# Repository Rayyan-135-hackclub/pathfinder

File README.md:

# pathfinder
Making a PCB for the first time

## Update 1: 6/11/25 Thursday 15 working time

I have started work on the PCB but I have got an error message as I was trying to download the code for the lights. Will try later or in school.
Also hackatime is not recording the time I put into this project and gives error message "Repo url is not clonable." It needs to be sorted out next hackclub.

## Update 2: 7/11/25 Friday 30m working time
Error fixed and I added resistors and wires (in the form of buttons) to the components. I think I have completed the PCB. I made a mistake and deleted everything but I restored it. (most of the time im figuring out what went wrong so it may not be recorded)

Finished Schematic:

## Update 3: 17/11/25 Saturday 20m working time

Watching the video: https://www.youtube.com/watch?v=MFTP7uMzt1s and trying to figure out how to arrange the wires on the PCB editor. Will continue next time.

What I have done so far:

## Update 4: 19/11/25 Wednesday 20m working time

I have completed the routing and I am cuurrently starting the 3D stuff.

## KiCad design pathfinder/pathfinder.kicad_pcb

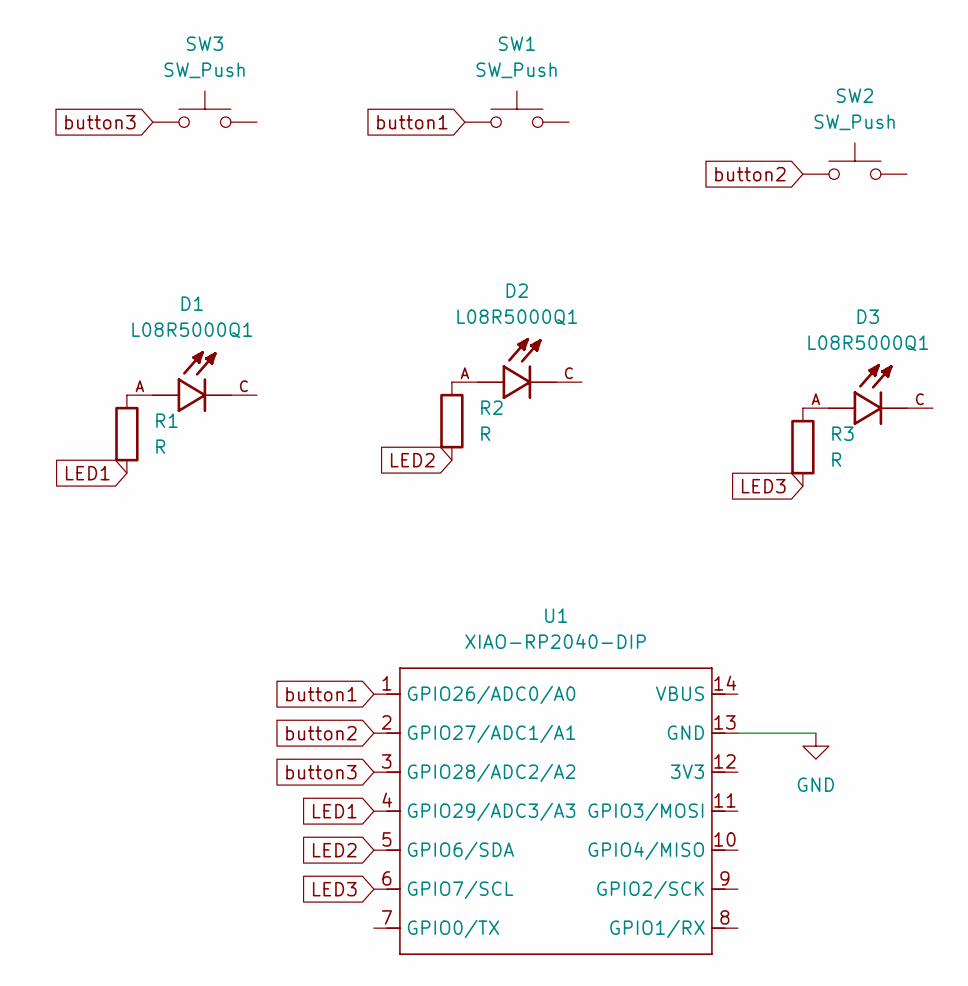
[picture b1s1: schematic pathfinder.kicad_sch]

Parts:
D1, D2, D3: L08R5000Q1; LEDRD254W57D500H1070; PARTREV NA
R1, R2, R3: R; R_Axial_DIN0204_L3.6mm_D1.6mm_P7.62mm_Horizontal
SW1, SW2, SW3: SW_Push; SW_Cherry_MX_1.00u_PCB
U1: XIAO-RP2040-DIP

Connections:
GND: U1.13 (GND)
LED1: R1.2, U1.4 (GPIO29/ADC3/A3)
LED2: R2.2, U1.5 (GPIO6/SDA)
LED3: R3.2, U1.6 (GPIO7/SCL)
unnamed: D1.A, R1.1
unnamed: D2.A, R2.1
unnamed: D3.A, R3.1
button1: SW1.1, U1.1 (GPIO26/ADC0/A0)
button2: SW2.1, U1.2 (GPIO27/ADC1/A1)
button3: SW3.1, U1.3 (GPIO28/ADC2/A2)

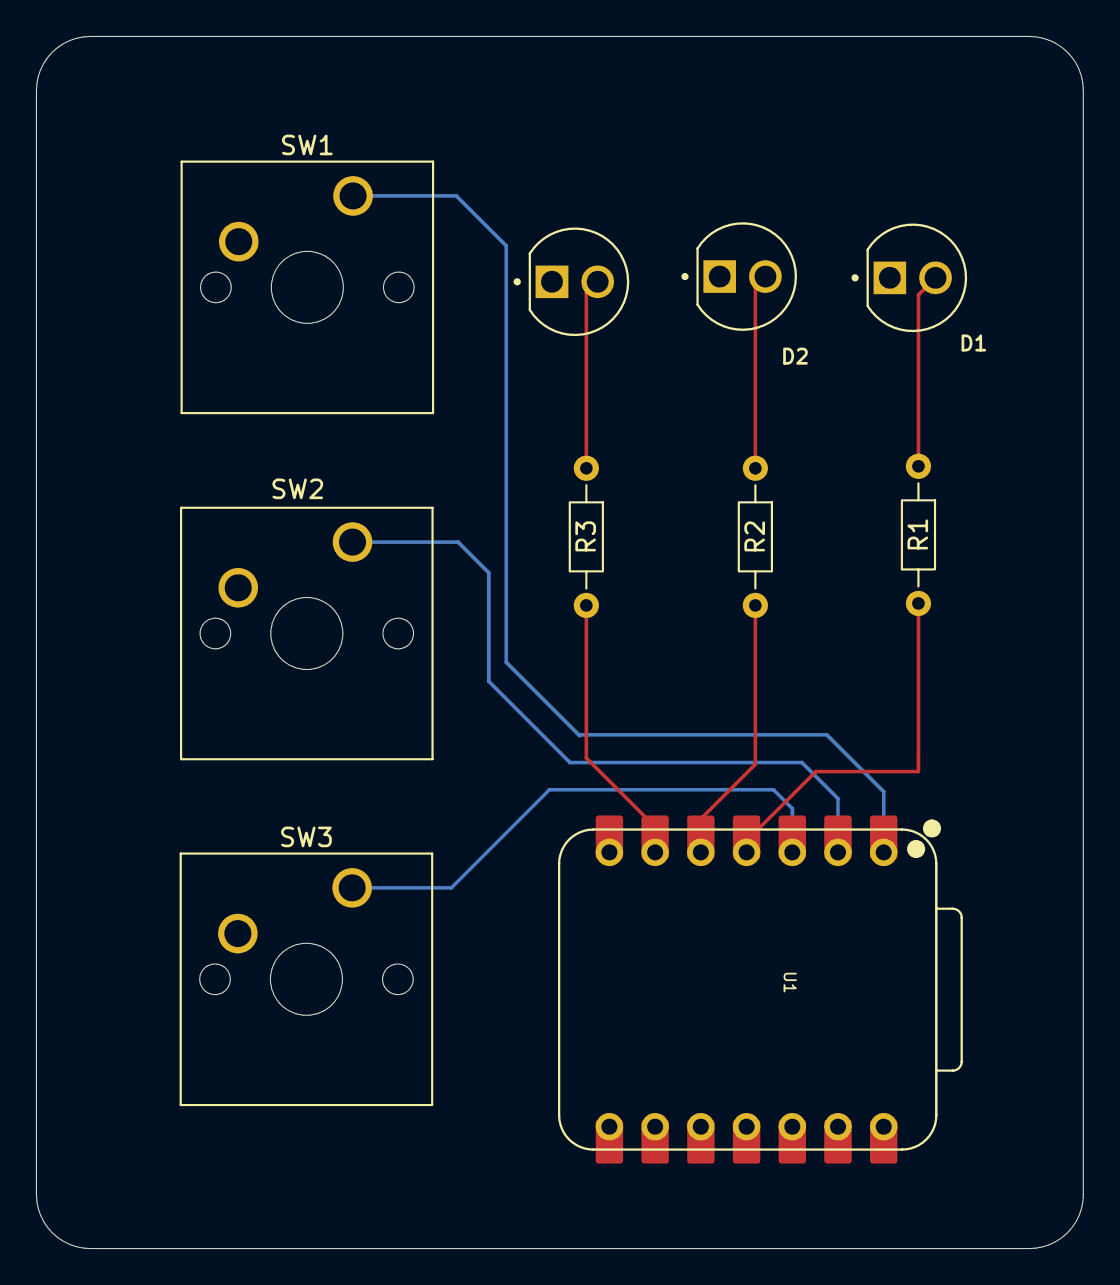
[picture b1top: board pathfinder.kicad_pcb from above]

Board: 2 copper layers, 58.2 x 67.3 mm, 10 parts (0 on the bottom side), 9 nets.

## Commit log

2025-11-06 Add files via upload
    Just started work on pcb, I need to start making the LED's next but there seems to be an error message so I'll try later or in school
2025-11-06 Add progress updates for PCB project
    Added updates regarding PCB progress and issues encountered.
2025-11-06 Revise updates in README.md with new information
    Updated project updates with new date and details.
2025-11-06 Fix formatting issue in README.md
2025-11-07 Just some minor changes
    Added lights to the symbol library
2025-11-07 Update README with project progress and issues
2025-11-07 Pathfinder update to
    Completed pathfinder by adding resistors, wires and a ground
2025-11-07 Realoading pathfinder filles after accidentally deleting them
    im just starting in github
2025-11-07 Fix error and update PCB completion details
    Restored deleted content and updated PCB completion status.
2025-11-12 Added a file
2025-11-14 Add to footprint libraries
2025-11-14 Improve README formatting and section headings
    Updated formatting and headings in README for clarity.
2025-11-14 Fix formatting and typos in README updates
    Corrected formatting of update headings and fixed minor typos.
2025-11-18 Revise project updates with working time entries
    Updated project updates with working time and additional details.
2025-11-18 Revise README with project updates and images
    Updated project progress and fixed errors in the PCB design. Added images of the schematic and current work.
2025-11-18 Started working on the PCB Editor
2025-11-19 Fix formatting issue in README header
2025-11-19 Updated
    I have done the routing and I am currently working on the 3D stuff
2025-11-19 Revise working time and add PCB updates
    Updated working time entries and added new updates on PCB progress.
